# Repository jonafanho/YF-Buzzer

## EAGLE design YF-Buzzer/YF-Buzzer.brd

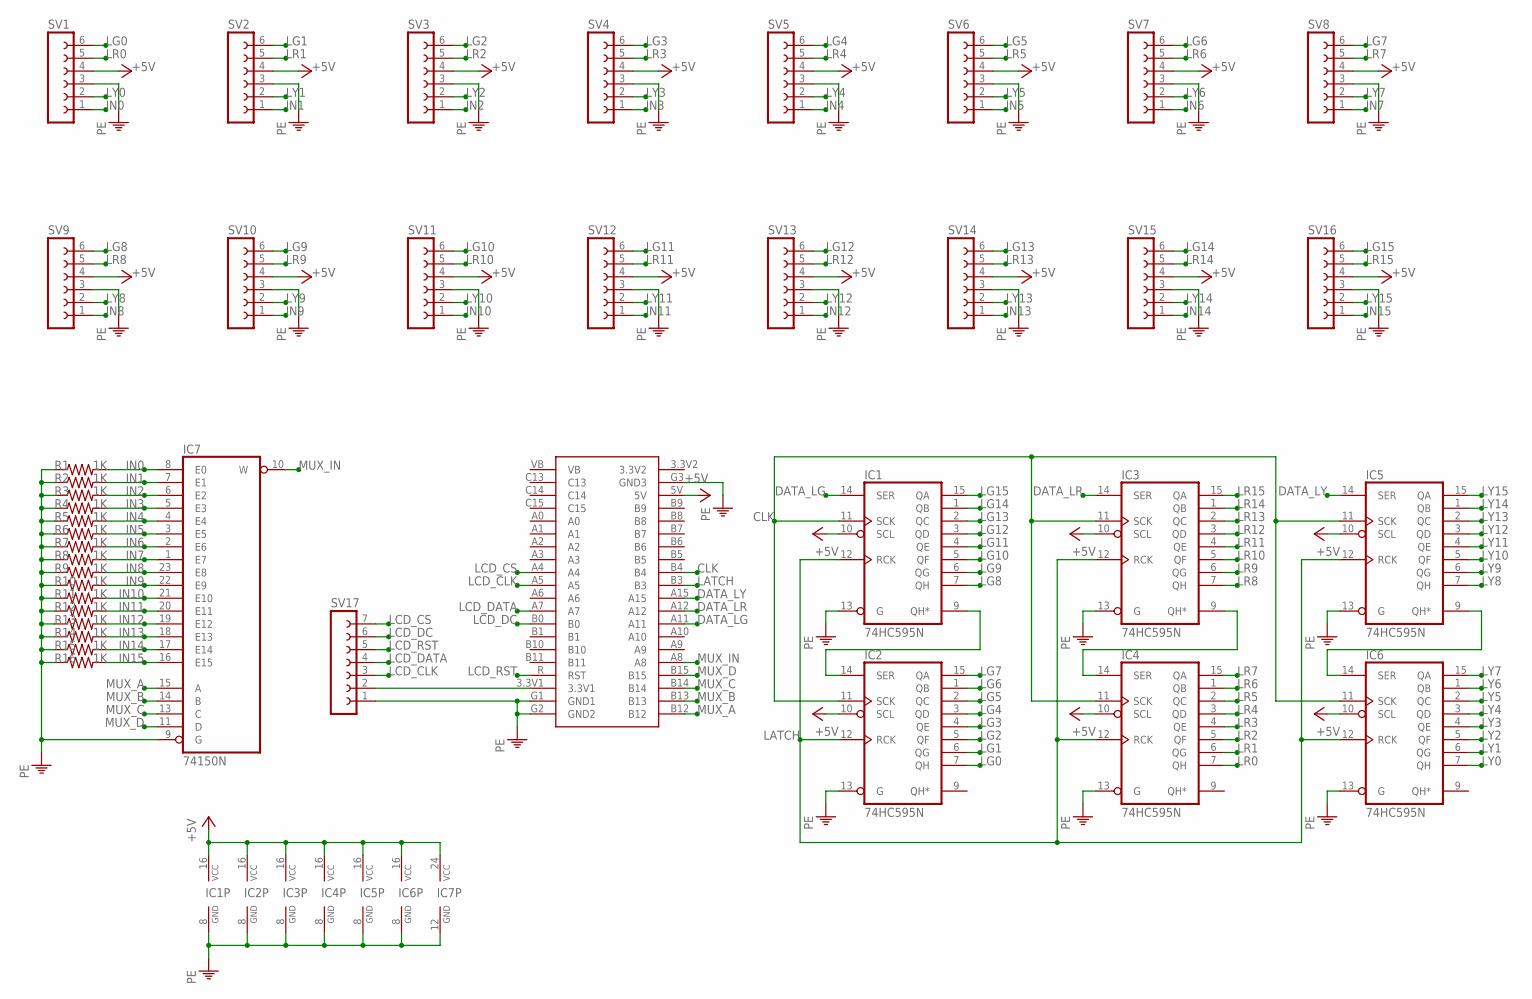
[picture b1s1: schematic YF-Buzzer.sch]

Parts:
IC1, IC2, IC3, IC4, IC5, IC6: 74HC595N; DIL16
IC7: 74150N; DIL24-6
MCU1: STM32-BLUE
R1, R2, R3, R4, R5, R6, R7, R8, R9, R10, R11, R12, R13, R14, R15, R16: 1K; 0207/10
SV1, SV2, SV3, SV4, SV5, SV6, SV7, SV8, SV9, SV10, SV11, SV12, SV13, SV14, SV15, SV16: FE06-1; FE06
SV17: FE07-1; FE07

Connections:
3.3V2: MCU1.3.3V2
+5V: IC1.10 (SCL), IC1.16 (VCC), IC2.10 (SCL), IC2.16 (VCC), IC3.10 (SCL), IC3.16 (VCC), IC4.10 (SCL), IC4.16 (VCC), IC5.10 (SCL), IC5.16 (VCC), IC6.10 (SCL), IC6.16 (VCC), IC7.24 (VCC), MCU1.5V, SV1.4, SV2.4, SV3.4, SV4.4, SV5.4, SV6.4, SV7.4, SV8.4, SV9.4, SV10.4, SV11.4, SV12.4, SV13.4, SV14.4, SV15.4, SV16.4
CLK: IC1.11 (SCK), IC2.11 (SCK), IC3.11 (SCK), IC4.11 (SCK), IC5.11 (SCK), IC6.11 (SCK), MCU1.B4
DATA_LG: IC1.14 (SER), MCU1.A11
DATA_LR: IC3.14 (SER), MCU1.A12
DATA_LY: IC5.14 (SER), MCU1.A15
IN0: IC7.8 (E0), R1.2, SV1.1
IN1: IC7.7 (E1), R2.2, SV2.1
IN2: IC7.6 (E2), R3.2, SV3.1
IN3: IC7.5 (E3), R4.2, SV4.1
IN4: IC7.4 (E4), R5.2, SV5.1
IN5: IC7.3 (E5), R6.2, SV6.1
IN6: IC7.2 (E6), R7.2, SV7.1
IN7: IC7.1 (E7), R8.2, SV8.1
IN8: IC7.23 (E8), R9.2, SV9.1
IN9: IC7.22 (E9), R10.2, SV10.1
IN10: IC7.21 (E10), R11.2, SV11.1
IN11: IC7.20 (E11), R12.2, SV12.1
IN12: IC7.19 (E12), R13.2, SV13.1
IN13: IC7.18 (E13), R14.2, SV14.1
IN14: IC7.17 (E14), R15.2, SV15.1
IN15: IC7.16 (E15), R16.2, SV16.1
LATCH: IC1.12 (RCK), IC2.12 (RCK), IC3.12 (RCK), IC4.12 (RCK), IC5.12 (RCK), IC6.12 (RCK), MCU1.B3
LCD_CLK: MCU1.A5, SV17.3
LCD_CS: MCU1.A4, SV17.7
LCD_DATA: MCU1.A7, SV17.4
LCD_DC: MCU1.B0, SV17.6
LCD_RST: MCU1.R (RST), SV17.5
LG0: IC2.7 (QH), SV1.6
LG1: IC2.6 (QG), SV2.6
LG2: IC2.5 (QF), SV3.6
LG3: IC2.4 (QE), SV4.6
LG4: IC2.3 (QD), SV5.6
LG5: IC2.2 (QC), SV6.6
LG6: IC2.1 (QB), SV7.6
LG7: IC2.15 (QA), SV8.6
LG8: IC1.7 (QH), SV9.6
LG9: IC1.6 (QG), SV10.6
LG10: IC1.5 (QF), SV11.6
LG11: IC1.4 (QE), SV12.6
LG12: IC1.3 (QD), SV13.6
LG13: IC1.2 (QC), SV14.6
LG14: IC1.1 (QB), SV15.6
LG15: IC1.15 (QA), SV16.6
LR0: IC4.7 (QH), SV1.5
LR1: IC4.6 (QG), SV2.5
LR2: IC4.5 (QF), SV3.5
LR3: IC4.4 (QE), SV4.5
LR4: IC4.3 (QD), SV5.5
LR5: IC4.2 (QC), SV6.5
LR6: IC4.1 (QB), SV7.5
LR7: IC4.15 (QA), SV8.5
LR8: IC3.7 (QH), SV9.5
LR9: IC3.6 (QG), SV10.5
LR10: IC3.5 (QF), SV11.5
LR11: IC3.4 (QE), SV12.5
LR12: IC3.3 (QD), SV13.5
LR13: IC3.2 (QC), SV14.5
LR14: IC3.1 (QB), SV15.5
LR15: IC3.15 (QA), SV16.5
LY0: IC6.7 (QH), SV1.2
LY1: IC6.6 (QG), SV2.2
LY2: IC6.5 (QF), SV3.2
LY3: IC6.4 (QE), SV4.2
LY4: IC6.3 (QD), SV5.2
LY5: IC6.2 (QC), SV6.2
LY6: IC6.1 (QB), SV7.2
LY7: IC6.15 (QA), SV8.2
LY8: IC5.7 (QH), SV9.2
LY9: IC5.6 (QG), SV10.2
LY10: IC5.5 (QF), SV11.2
LY11: IC5.4 (QE), SV12.2
LY12: IC5.3 (QD), SV13.2
LY13: IC5.2 (QC), SV14.2
LY14: IC5.1 (QB), SV15.2
LY15: IC5.15 (QA), SV16.2
MUX_A: IC7.15 (A), MCU1.B12
MUX_B: IC7.14 (B), MCU1.B13
MUX_C: IC7.13 (C), MCU1.B14
MUX_D: IC7.11 (D), MCU1.B15
MUX_IN: IC7.10 (W), MCU1.A8
unnamed: IC1.9 (QH*), IC2.14 (SER)
unnamed: IC3.9 (QH*), IC4.14 (SER)
unnamed: IC5.9 (QH*), IC6.14 (SER)
unnamed: MCU1.3.3V1, SV17.2
PE: IC1.8 (GND), IC1.13 (G), IC2.8 (GND), IC2.13 (G), IC3.8 (GND), IC3.13 (G), IC4.8 (GND), IC4.13 (G), IC5.8 (GND), IC5.13 (G), IC6.8 (GND), IC6.13 (G), IC7.9 (G), IC7.12 (GND), MCU1.G1 (GND1), MCU1.G2 (GND2), MCU1.G3 (GND3), R1.1, R2.1, R3.1, R4.1, R5.1, R6.1, R7.1, R8.1, R9.1, R10.1, R11.1, R12.1, R13.1, R14.1, R15.1, R16.1, SV1.3, SV2.3, SV3.3, SV4.3, SV5.3, SV6.3, SV7.3, SV8.3, SV9.3, SV10.3, SV11.3, SV12.3, SV13.3, SV14.3, SV15.3, SV16.3, SV17.1
VB: MCU1.VB

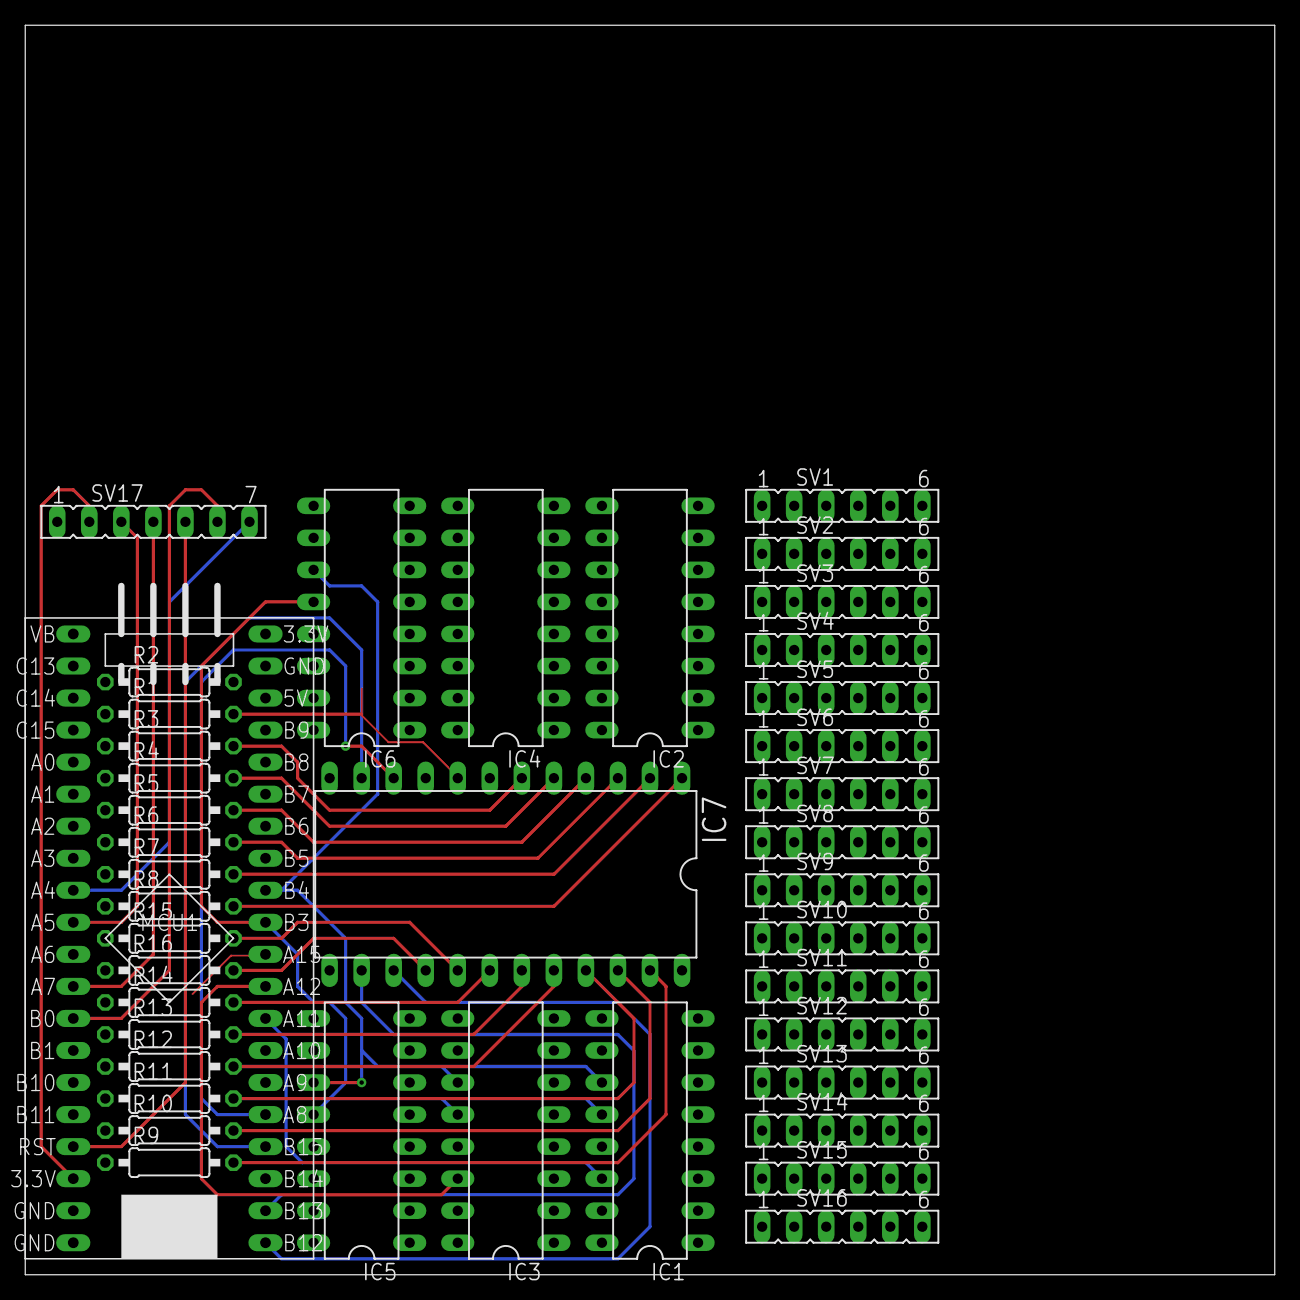
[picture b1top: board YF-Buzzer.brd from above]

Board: 2 copper layers, 99.1 x 99.1 mm, 41 parts (0 on the bottom side), 85 nets.

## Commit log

2019-05-02 Created a circuit schematic.
2019-05-03 Added code for shifting data into registers and reading the demux.
2019-05-04 Added the multiplexer and microcontroller to the circuit.
2019-05-04 Finished the shift register circuits and began layout of the PCB.
2019-07-06 Autorouted the rest of the main circuit.
2019-12-20 Removed LED's and cleaned up the circuit.
